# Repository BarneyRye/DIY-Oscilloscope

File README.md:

# DIY Osciliscope
Design based on a **STM32F405RGT6**, with 2 options to connect up to 2 seperate leads. <br>
Used a 240x320 TFT ILI9341 screen module over SPI. <br>
[Example Screen: 2.8-inch SPI LCD Module 240 * 320 TFT Module ILI9341](https://www.amazon.co.uk/DIGISHUO-2-8-inch-ILI9341-occupies-Display/dp/B0DPZ3B171?source=ps-sl-shoppingads-lpcontext&ref_=fplfs&psc=1&smid=A3GCGSGY68R0P6&utm_source=chatgpt.com) <br>
Max inputs of +/- 20V, 40Vpp. <br>
USB-C connection for power or streaming waveform to seprate device.

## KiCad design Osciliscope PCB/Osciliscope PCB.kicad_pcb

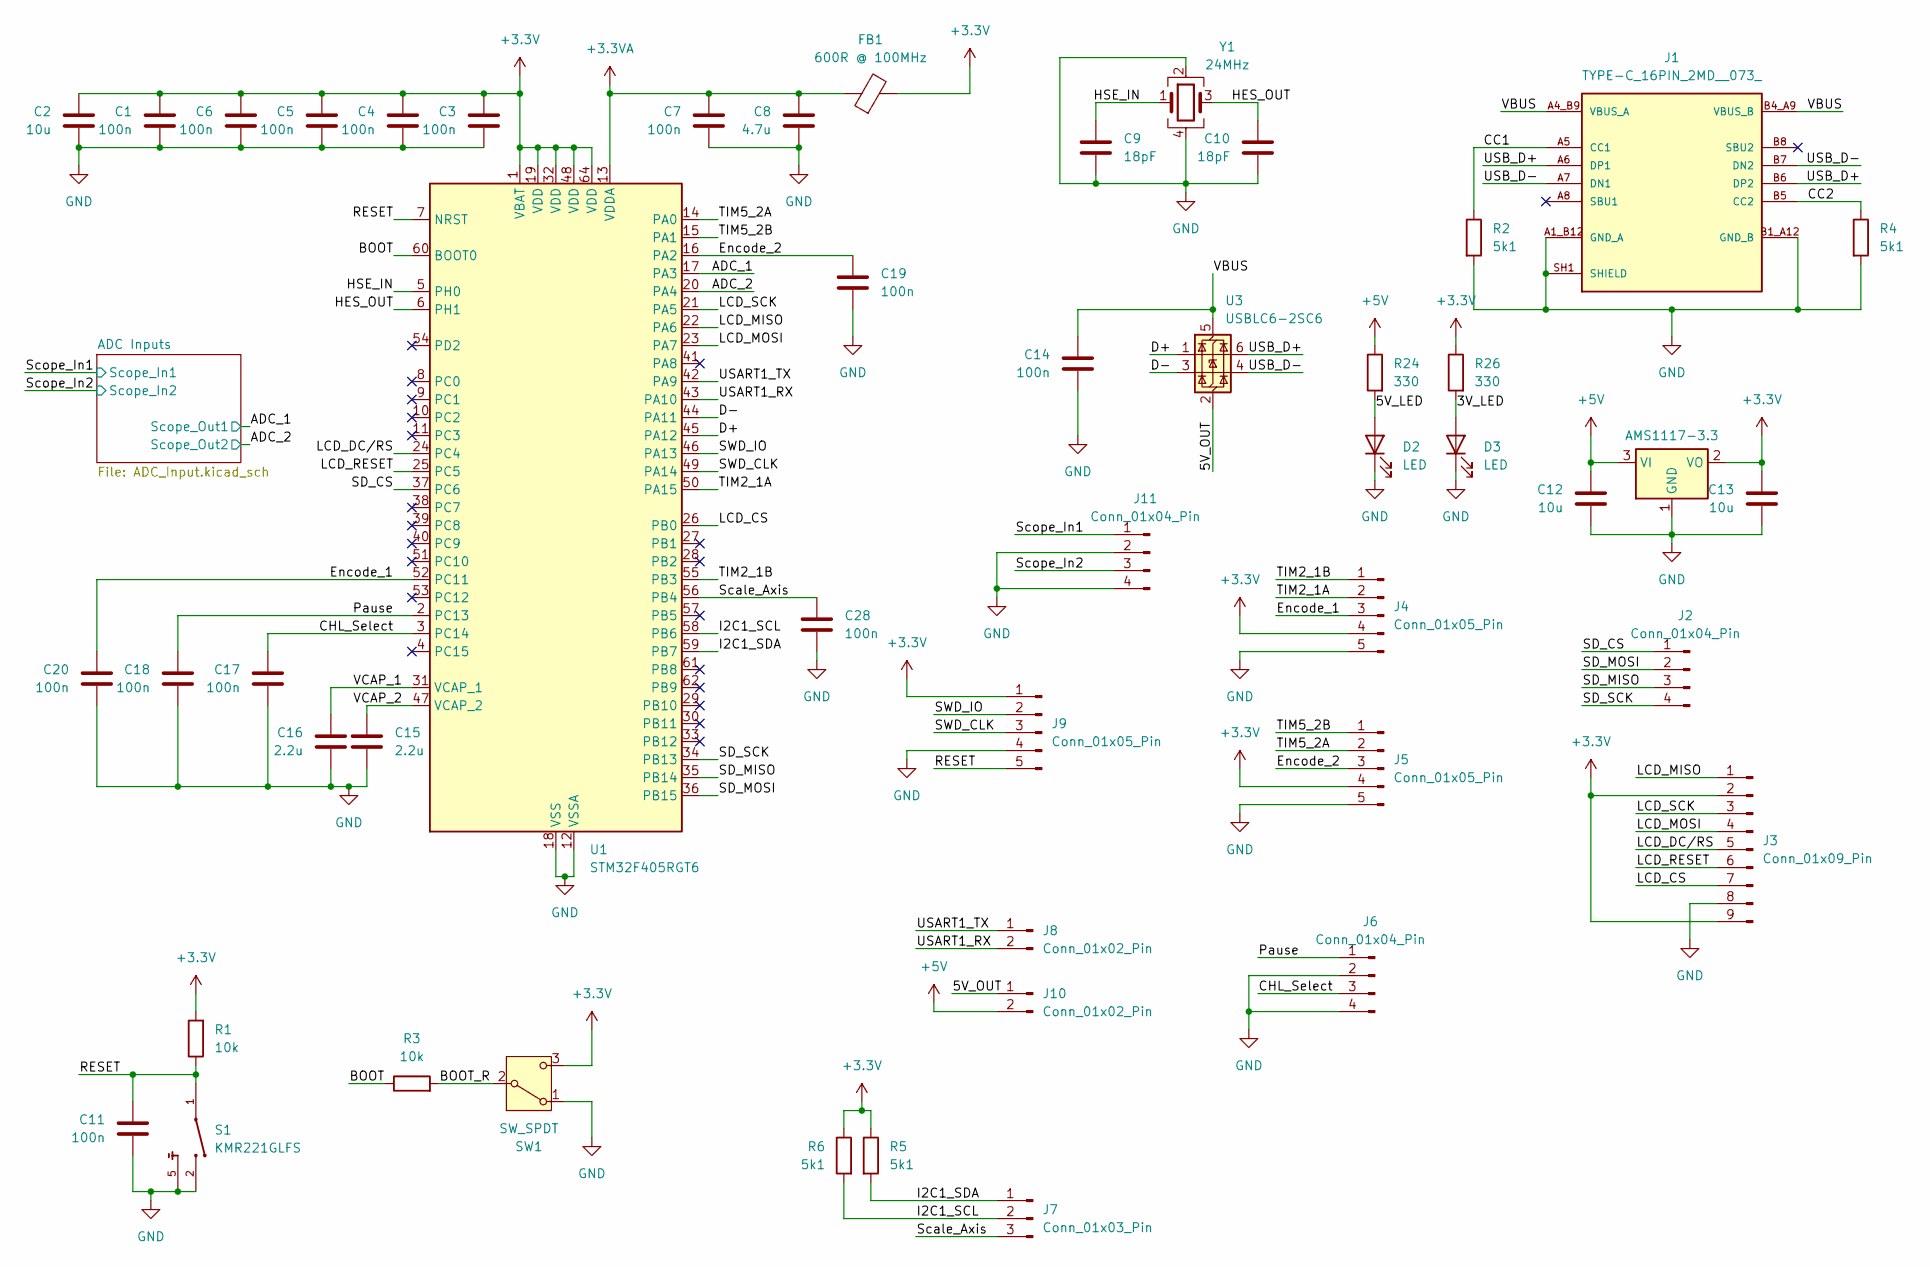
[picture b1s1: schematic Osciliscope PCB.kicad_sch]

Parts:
C1, C3, C4, C5, C6, C7, C11, C14, C17, C18, C19, C20, C28: 100n; C_0402_1005Metric
C2, C12, C13: 10u; C_0805_2012Metric
C8: 4.7u; C_0603_1608Metric
C9, C10: 18pF; C_0402_1005Metric
C15, C16: 2.2u; C_0603_1608Metric
D2, D3: LED; C_0805_2012Metric
FB1: 600R @ 100MHz; C_0805_2012Metric
J1: TYPE-C_16PIN_2MD__073_; SHOUHAN_TYPE-C_16PIN_2MD__073_; Part NO. C393939
J2, J6, J11: Conn_01x04_Pin; PinHeader_1x04_P2.54mm_Vertical; Part NO. C2905435
J3: Conn_01x09_Pin; PinHeader_1x09_P2.54mm_Vertical; Part NO. C2932701
J4, J5, J9: Conn_01x05_Pin; PinHeader_1x05_P2.54mm_Vertical; Part NO. C2932699
J7: Conn_01x03_Pin; PinHeader_1x03_P2.54mm_Vertical; Part NO. C2932698
J8, J10: Conn_01x02_Pin; PinHeader_1x02_P2.54mm_Vertical; Part NO. C2932698
R1, R3: 10k; C_0402_1005Metric
R2, R4, R5, R6: 5k1; C_0402_1005Metric
R24, R26: 330; C_0603_1608Metric
S1: KMR221GLFS; SW_KMR221GLFS; Part NO. C72443
SW1: SW_SPDT; SW-SMD_SSSS810701; Part NO. C97433
U1: STM32F405RGT6; LQFP-64_10x10mm_P0.5mm; Part NO. C15742
U2: AMS1117-3.3; SOT-223-3_TabPin2; Part NO. C2688239
U3: USBLC6-2SC6; SOT-23-6; Part NO. C7519
Y1: 24MHz; Crystal_SMD_3225-4Pin_3.2x2.5mm; Part NO. C70590

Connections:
+3.3V: C1.1, C2.1, C3.1, C4.1, C5.1, C6.1, C13.1, FB1.2, J3.2, J3.9, J4.4, J5.4, J9.1, R1.2, R5.1, R6.1, R26.1, SW1.3 (C), U1.1 (VBAT), U1.19 (VDD), U1.32 (VDD), U1.48 (VDD), U1.64 (VDD), U2.2 (VO); also elsewhere on the board
+3.3VA: C7.1, C8.1, FB1.1, U1.13 (VDDA)
+5V: C12.1, J10.2, R24.1, U2.3 (VI)
/3V_LED: D3.2 (A), R26.2
/5V_LED: D2.2 (A), R24.2
/5V_OUT: J10.1, U3.2 (GND)
/ADC_1: U1.17 (PA3); also elsewhere on the board
/ADC_2: U1.20 (PA4); also elsewhere on the board
/BOOT: R3.1, U1.60 (BOOT0)
/BOOT_R: R3.2, SW1.2 (B)
/CC1: J1.A5 (CC1), R2.1
/CC2: J1.B5 (CC2), R4.1
/CHL_Select: C17.1, J6.3, U1.3 (PC14)
/D+: U1.45 (PA12), U3.1 (I/O1)
/D-: U1.44 (PA11), U3.3 (I/O2)
/Encode_1: C20.1, J4.3, U1.52 (PC11)
/Encode_2: C19.1, J5.3, U1.16 (PA2)
/HES_OUT: C10.1, U1.6 (PH1), Y1.3
/HSE_IN: C9.1, U1.5 (PH0), Y1.1
/I2C1_SCL: J7.2, R6.2, U1.58 (PB6)
/I2C1_SDA: J7.1, R5.2, U1.59 (PB7)
/LCD_CS: J3.7, U1.26 (PB0)
/LCD_DC/RS: J3.5, U1.24 (PC4)
/LCD_MISO: J3.1, U1.22 (PA6)
/LCD_MOSI: J3.4, U1.23 (PA7)
/LCD_RESET: J3.6, U1.25 (PC5)
/LCD_SCK: J3.3, U1.21 (PA5)
/Pause: C18.1, J6.1, U1.2 (PC13)
/RESET: C11.1, J9.5, R1.1, S1.1, S1.4, U1.7 (NRST)
/SD_CS: J2.1, U1.37 (PC6)
/SD_MISO: J2.3, U1.35 (PB14)
/SD_MOSI: J2.2, U1.36 (PB15)
/SD_SCK: J2.4, U1.34 (PB13)
/SWD_CLK: J9.3, U1.49 (PA14)
/SWD_IO: J9.2, U1.46 (PA13)
/Scale_Axis: C28.1, J7.3, U1.56 (PB4)
/Scope_In1: J11.1; also elsewhere on the board
/Scope_In2: J11.3; also elsewhere on the board
/TIM2_1A: J4.2, U1.50 (PA15)
/TIM2_1B: J4.1, U1.55 (PB3)
/TIM5_2A: J5.2, U1.14 (PA0)
/TIM5_2B: J5.1, U1.15 (PA1)
/USART1_RX: J8.2, U1.43 (PA10)
/USART1_TX: J8.1, U1.42 (PA9)
/USB_D+: J1.A6 (DP1), J1.B6 (DP2), U3.6 (I/O1)
/USB_D-: J1.A7 (DN1), J1.B7 (DN2), U3.4 (I/O2)
/VBUS: C14.1, J1.A4_B9 (VBUS_A), J1.B4_A9 (VBUS_B), U3.5 (VBUS)
/VCAP_1: C16.1, U1.31 (VCAP_1)
/VCAP_2: C15.1, U1.47 (VCAP_2)
GND: C1.2, C2.2, C3.2, C4.2, C5.2, C6.2, C7.2, C8.2, C9.2, C10.2, C11.2, C12.2, C13.2, C14.2, C15.2, C16.2, C17.2, C18.2, C19.2, C20.2, C28.2, D2.1 (K), D3.1 (K), J1.A1_B12 (GND_A), J1.B1_A12 (GND_B), J1.SH1 (SHIELD), J1.SH2 (SHIELD), J1.SH3 (SHIELD), J1.SH4 (SHIELD), J3.8, J4.5, J5.5, J6.2, J6.4, J9.4, J11.2, J11.4, R2.2, R4.2, S1.2, S1.3, S1.5, SW1.1 (A), U1.12 (VSSA), U1.18 (VSS), U1.63 (VSS), U2.1 (GND), Y1.2, Y1.4; also elsewhere on the board

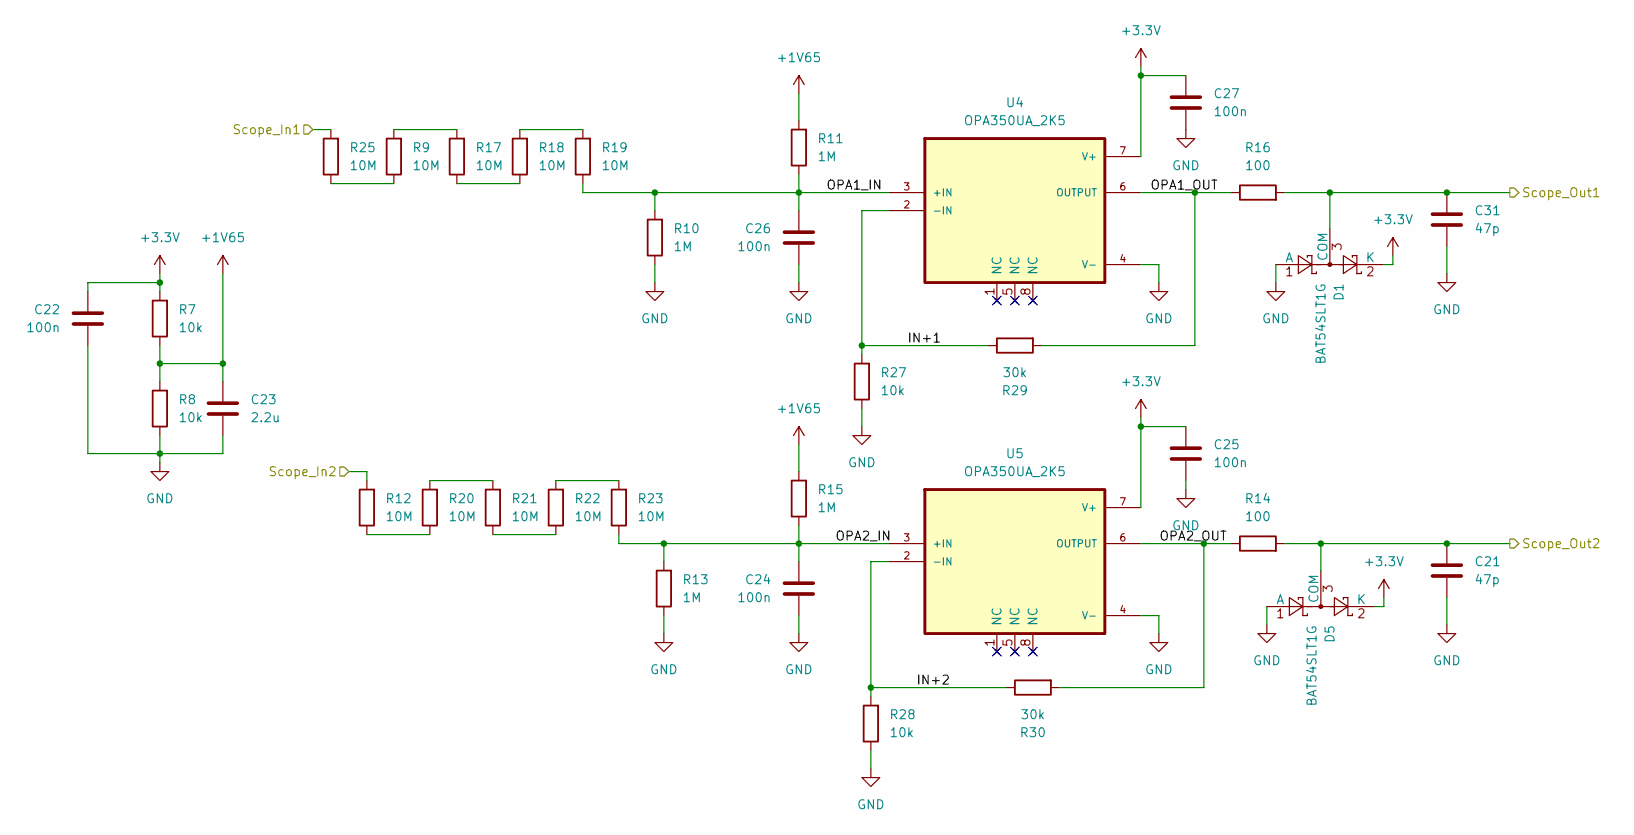
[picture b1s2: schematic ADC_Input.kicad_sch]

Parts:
C21, C31: 47p; C_0402_1005Metric
C22, C24, C25, C26, C27: 100n; C_0402_1005Metric
C23: 2.2u; C_0603_1608Metric
D1, D5: BAT54SLT1G; SOT-23
R7, R8, R27, R28: 10k; C_0402_1005Metric
R9, R12, R17, R18, R19, R20, R21, R22, R23, R25: 10M; C_0402_1005Metric
R10, R11, R13, R15: 1M; C_0402_1005Metric
R14, R16: 100; C_0402_1005Metric
R29, R30: 30k; C_0402_1005Metric
U4, U5: OPA350UA_2K5; SOIC127P599X175-8N; Part NO. C13388

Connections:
+1V65: C23.1, R7.1, R8.2, R11.2, R15.2
+3.3V: C22.1, C25.1, C27.1, D1.2 (K), D5.2 (K), R7.2, U4.7 (V+), U5.7 (V+); also elsewhere on the board
/ADC Inputs/IN+1: R27.2, R29.1, U4.2 (-IN)
/ADC Inputs/IN+2: R28.2, R30.1, U5.2 (-IN)
/ADC Inputs/OPA1_IN: C26.1, R10.2, R11.1, R19.1, U4.3 (+IN)
/ADC Inputs/OPA1_OUT: R16.1, R29.2, U4.6 (OUTPUT)
/ADC Inputs/OPA2_IN: C24.1, R13.2, R15.1, R23.1, U5.3 (+IN)
/ADC Inputs/OPA2_OUT: R14.1, R30.2, U5.6 (OUTPUT)
/ADC_1: C31.1, D1.3 (COM), R16.2; also elsewhere on the board
/ADC_2: C21.1, D5.3 (COM), R14.2; also elsewhere on the board
/Scope_In1: R25.2; also elsewhere on the board
/Scope_In2: R12.2; also elsewhere on the board
GND: C21.2, C22.2, C23.2, C24.2, C25.2, C26.2, C27.2, C31.2, D1.1 (A), D5.1 (A), R8.1, R10.1, R13.1, R27.1, R28.1, U4.4 (V-), U5.4 (V-); also elsewhere on the board
unnamed: R12.1, R20.1
unnamed: R17.1, R18.1
unnamed: R9.2, R17.2
unnamed: R18.2, R19.2
unnamed: R20.2, R21.2
unnamed: R21.1, R22.1
unnamed: R22.2, R23.2
unnamed: R9.1, R25.1

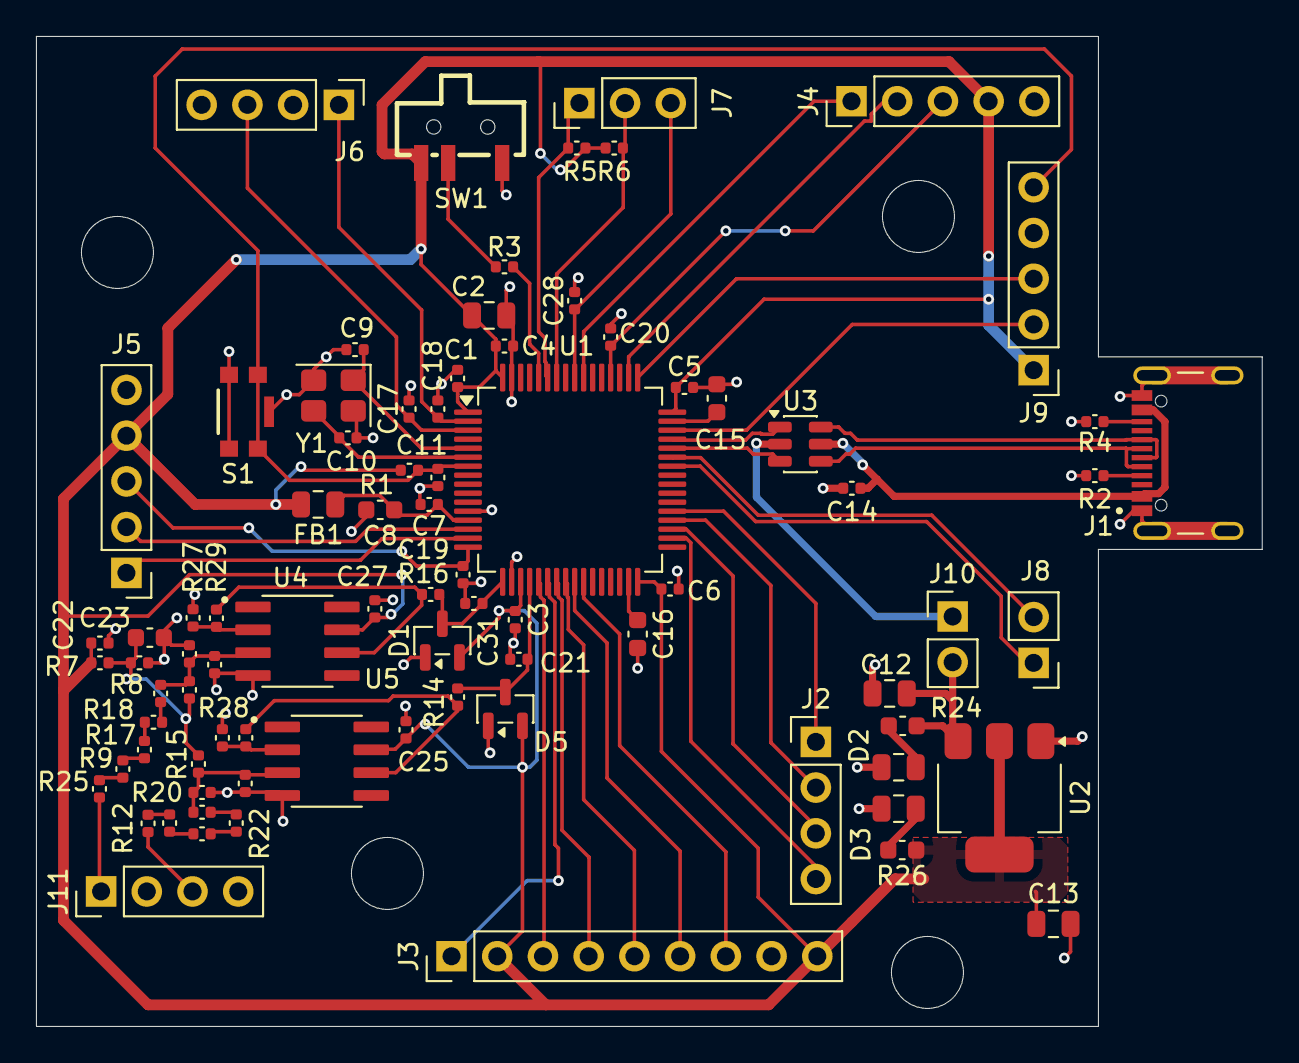
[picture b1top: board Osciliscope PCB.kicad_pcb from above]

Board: 2 copper layers, 68.1 x 55.0 mm, 83 parts (0 on the bottom side), 65 nets.

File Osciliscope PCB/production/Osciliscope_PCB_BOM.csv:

"Reference","Qty","Value","DNP","Exclude from BOM","Exclude from Board","Footprint","Datasheet","Part NO.","Description"
"C9,C10","2","18pF","","","","Capacitor_SMD:C_0805_2012Metric","https://jlcpcb.com/api/file/downloadByFileSystemAccessId/857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","C1797","0805CG180J500NT"
"C21,C31","2","47p","","","","Diode_SMD:D_0805_2012Metric","https://jlcpcb.com/api/file/downloadByFileSystemAccessId/857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","C14857","CL21C470JBANNNC"
"C1,C3,C4,C5,C6,C7,C11,C14,C17,C18,C19,C20,C22,C24,C25,C26,C27","17","100n","","","","Capacitor_SMD:C_0805_2012Metric","https://jlcpcb.com/api/file/downloadByFileSystemAccessId/858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","C28233","CL21B104KCFNNNE"
"C15,C16,C23","3","2.2u","","","","Capacitor_SMD:C_0805_2012Metric","https://jlcpcb.com/api/file/downloadByFileSystemAccessId/858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","C377773","CL21A225KBQNNNE"
"C8","1","4.7u","","","","Capacitor_SMD:C_0805_2012Metric","https://jlcpcb.com/api/file/downloadByFileSystemAccessId/855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","C1779","CL21A475KAQNNNE"
"C2,C12,C13","3","10u","","","","Capacitor_SMD:C_0805_2012Metric","https://jlcpcb.com/api/file/downloadByFileSystemAccessId/857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","C15850","CL21A106KAYNNNE"
"R14,R16","2","100","","","","Resistor_SMD:R_0805_2012Metric","https://jlcpcb.com/api/file/downloadByFileSystemAccessId/856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","C17408","0805W8F1000T5E"
"R24,R26","2","330","","","","Resistor_SMD:R_0805_2012Metric","https://jlcpcb.com/api/file/downloadByFileSystemAccessId/857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","C17630","0805W8F3300T5E"
"R1,R3","2","10k","","","","Resistor_SMD:R_0805_2012Metric","https://jlcpcb.com/api/file/downloadByFileSystemAccessId/856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","C17414","0805W8F1002T5E"
"R7,R8,R10,R11,R13,R15","6","1M","","","","Resistor_SMD:R_0805_2012Metric","https://jlcpcb.com/api/file/downloadByFileSystemAccessId/857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","C17514","0805W8F1004T5E"
"R9,R12,R17,R18,R19,R20,R21,R22,R23,R25","10","10M","","","","Resistor_SMD:R_0805_2012Metric","https://jlcpcb.com/api/file/downloadByFileSystemAccessId/857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","C26108","0805W8F1005T5E"
"Y1","1","24MHz","","","","Crystal:Crystal_SMD_3225-4Pin_3.2x2.5mm","https://jlcpcb.com/api/file/downloadByFileSystemAccessId/858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","C70590","X322524MOB4SI"
"R2,R4,R5,R6","4","5k1","","","","Resistor_SMD:R_0805_2012Metric","https://jlcpcb.com/api/file/downloadByFileSystemAccessId/857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","C27834","0805W8F5101T5E"
"FB1","1","600R @ 100MHz","","","","Capacitor_SMD:C_0805_2012Metric","https://jlcpcb.com/api/file/downloadByFileSystemAccessId/856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","C1017","GZ2012D601TF"
"U2","1","AMS1117-3.3","","","","Package_TO_SOT_SMD:SOT-223-3_TabPin2","http://www.advanced-monolithic.com/pdf/ds1117.pdf","C2688239","AMS1117-3.3V"
"D1,D5","2","BAT54SLT1G","","","","Package_TO_SOT_SMD:SOT-23","https://www.diodes.com/assets/Datasheets/ds11005.pdf","","BAT54SLT1G"
"J8,J10","2","Conn_01x02_Pin","","","","Connector_PinHeader_2.54mm:PinHeader_1x02_P2.54mm_Vertical","https://jlcpcb.com/api/file/downloadByFileSystemAccessId/858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","C2932698","KH-2.54PH180-1X2P-L11.5"
"J7","1","Conn_01x03_Pin","","","","Connector_PinHeader_2.54mm:PinHeader_1x03_P2.54mm_Vertical","https://jlcpcb.com/api/file/downloadByFileSystemAccessId/858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","C2932698","KH-2.54PH180-1X3P-L11.5"
"J2,J6,J11","3","Conn_01x04_Pin","","","","Connector_PinHeader_2.54mm:PinHeader_1x04_P2.54mm_Vertical","https://jlcpcb.com/api/file/downloadByFileSystemAccessId/858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","C2905435","KH-2.54PH180-1X4P-L11.5"
"J4,J5,J9","3","Conn_01x05_Pin","","","","Connector_PinHeader_2.54mm:PinHeader_1x05_P2.54mm_Vertical","https://jlcpcb.com/api/file/downloadByFileSystemAccessId/858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","C2932699","KH-2.54PH180-1X5P-L11.5"
"J3","1","Conn_01x09_Pin","","","","Connector_PinHeader_2.54mm:PinHeader_1x09_P2.54mm_Vertical","https://jlcpcb.com/api/file/downloadByFileSystemAccessId/858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","C2932701","KH-2.54PH180-1X9P-L11.5"
"S1","1","KMR221GLFS","","","","02Footprints:SW_KMR221GLFS","https://jlcpcb.com/api/file/downloadByFileSystemAccessId/858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","C72443","KMR221GLFS"
"D2,D3","2","LED","","","","LED_SMD:LED_0805_2012Metric","https://www.lcsc.com/datasheet/C2295.pdf","C2295","KT-0805R"
"U4,U5","2","OPA350UA_2K5","","","","02Footprints:SOIC127P599X175-8N","https://www.ti.com/cn/lit/ds/symlink/opa350.pdf?ts=176895383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","C13388","OPA350UA/2K5"
"U1","1","STM32F405RGT6","","","","Package_QFP:LQFP-64_10x10mm_P0.5mm","https://www.st.com/resource/en/datasheet/stm32f405rg.pdf","C15742","STMicroelectronics Arm Cortex-M4 MCU, 1024KB flash, 192KB RAM, 168 MHz, 1.8-3.6V, 51 GPIO, LQFP64"
"SW1","1","SW_SPDT","","","","02Footprints:SW-SMD_SSSS810701","~","","Switch, single pole double throw"
"J1","1","TYPE-C_16PIN_2MD__073_","","","","02Footprints:SHOUHAN_TYPE-C_16PIN_2MD__073_","https://jlcpcb.com/api/file/downloadByFileSystemAccessId/858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","C393939","TYPE-C16PIN"
"U3","1","USBLC6-2SC6","","","","Package_TO_SOT_SMD:SOT-23-6","https://www.st.com/resource/en/datasheet/usblc6-2.pdf","C7519","Very low capacitance ESD protection diode, 2 data-line, SOT-23-6"

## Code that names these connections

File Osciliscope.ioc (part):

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Mcu.Name=STM32F405RGTx
Mcu.Package=LQFP64
Mcu.UserName=STM32F405RGTx
PA0-WKUP.Signal=S_TIM5_CH1
PA1.Signal=S_TIM5_CH2
PA10.Mode=Asynchronous
PA10.Signal=USART1_RX
PA11.Mode=Device_Only
PA11.Signal=USB_OTG_FS_DM
PA12.Mode=Device_Only
PA12.Signal=USB_OTG_FS_DP
PA13.GPIOParameters=GPIO_Label
PA13.GPIO_Label=SWD_IO
PA13.Mode=Serial_Wire
PA13.Signal=SYS_JTMS-SWDIO
PA14.GPIOParameters=GPIO_Label
PA14.GPIO_Label=SWD_CLK
PA14.Mode=Serial_Wire
PA14.Signal=SYS_JTCK-SWCLK
PA15.Signal=S_TIM2_CH1_ETR
PA2.GPIOParameters=GPIO_PuPd,GPIO_Label,GPIO_ModeDefaultEXTI
PA2.GPIO_Label=Encode_2
PA2.GPIO_ModeDefaultEXTI=GPIO_MODE_IT_FALLING
PA2.GPIO_PuPd=GPIO_PULLUP
PA2.Signal=GPXTI2
PA3.Signal=ADCx_IN3
PA4.Signal=ADCx_IN4
PA5.GPIOParameters=GPIO_Label
PA5.GPIO_Label=LCD_SCK
PA5.Mode=Full_Duplex_Master
PA5.Signal=SPI1_SCK
PA6.GPIOParameters=GPIO_Label
PA6.GPIO_Label=LCD_MISO
PA6.Mode=Full_Duplex_Master
PA6.Signal=SPI1_MISO
PA7.GPIOParameters=GPIO_Label
PA7.GPIO_Label=LCD_MOSI
PA7.Mode=Full_Duplex_Master
PA7.Signal=SPI1_MOSI
PA9.Mode=Asynchronous
PA9.Signal=USART1_TX
PB0.GPIOParameters=GPIO_Label
PB0.GPIO_Label=LCD_CS
PB0.Signal=GPIO_Output
PB13.GPIOParameters=GPIO_Label
PB13.GPIO_Label=SD_SCK
PB13.Mode=Full_Duplex_Master
PB13.Signal=SPI2_SCK
PB14.GPIOParameters=GPIO_Label
PB14.GPIO_Label=SD_MISO
PB14.Mode=Full_Duplex_Master
PB14.Signal=SPI2_MISO
PB15.GPIOParameters=GPIO_Label
PB15.GPIO_Label=SD_MOSI
PB15.Mode=Full_Duplex_Master
PB15.Signal=SPI2_MOSI
PB3.Signal=S_TIM2_CH2
PB4.GPIOParameters=GPIO_PuPd,GPIO_Label,GPIO_ModeDefaultEXTI
PB4.GPIO_Label=Scale_Axis
PB4.GPIO_ModeDefaultEXTI=GPIO_MODE_IT_FALLING
PB4.GPIO_PuPd=GPIO_PULLUP
PB4.Signal=GPXTI4
PB6.Mode=I2C
PB6.Signal=I2C1_SCL
PB7.Mode=I2C
PB7.Signal=I2C1_SDA
PC11.GPIOParameters=GPIO_PuPd,GPIO_Label,GPIO_ModeDefaultEXTI
PC11.GPIO_Label=Encode_1
PC11.GPIO_ModeDefaultEXTI=GPIO_MODE_IT_FALLING
PC11.GPIO_PuPd=GPIO_PULLUP
PC11.Signal=GPXTI11
PC13-ANTI_TAMP.GPIOParameters=GPIO_PuPd,GPIO_Label,GPIO_ModeDefaultEXTI
PC13-ANTI_TAMP.GPIO_Label=Pause
PC13-ANTI_TAMP.GPIO_ModeDefaultEXTI=GPIO_MODE_IT_FALLING
PC13-ANTI_TAMP.GPIO_PuPd=GPIO_PULLUP
PC13-ANTI_TAMP.Signal=GPXTI13
PC14-OSC32_IN.GPIOParameters=GPIO_PuPd,GPIO_Label,GPIO_ModeDefaultEXTI
PC14-OSC32_IN.GPIO_Label=CHL_Select
PC14-OSC32_IN.GPIO_ModeDefaultEXTI=GPIO_MODE_IT_FALLING
PC14-OSC32_IN.GPIO_PuPd=GPIO_PULLUP
PC14-OSC32_IN.Signal=GPXTI14
PC4.GPIOParameters=GPIO_Label
PC4.GPIO_Label=LCD_DC/RS
PC4.Signal=GPIO_Output
PC5.GPIOParameters=GPIO_Label
PC5.GPIO_Label=LCD_RESET
PC5.Signal=GPIO_Output
PC6.GPIOParameters=GPIO_Label
PC6.GPIO_Label=SD_CS
PC6.Signal=GPIO_Output
PH0-OSC_IN.Mode=HSE-External-Oscillator
PH0-OSC_IN.Signal=RCC_OSC_IN
PH1-OSC_OUT.Mode=HSE-External-Oscillator
PH1-OSC_OUT.Signal=RCC_OSC_OUT
RCC.HSE_VALUE=24000000
RCC.SYSCLKFreq_VALUE=168000000
RCC.SYSCLKSource=RCC_SYSCLKSOURCE_PLLCLK
board=custom

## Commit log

2026-01-22 Started main code and most of ILI9341 driver
2026-01-22 Quick Edit
2026-01-23 Edited Schematic
2026-01-23 Started main loop and added changes to screen function for allign
2026-01-23 Adding more block code
2026-01-23 Finishing up Code
2026-01-23 Cleaned up and fixed code
2026-01-24 Finished code, bug checked and also wrote code to print UI with ASCII font
2026-01-24 Finished PCB
2026-01-24 Removed old files
2026-01-28 Quick fix
